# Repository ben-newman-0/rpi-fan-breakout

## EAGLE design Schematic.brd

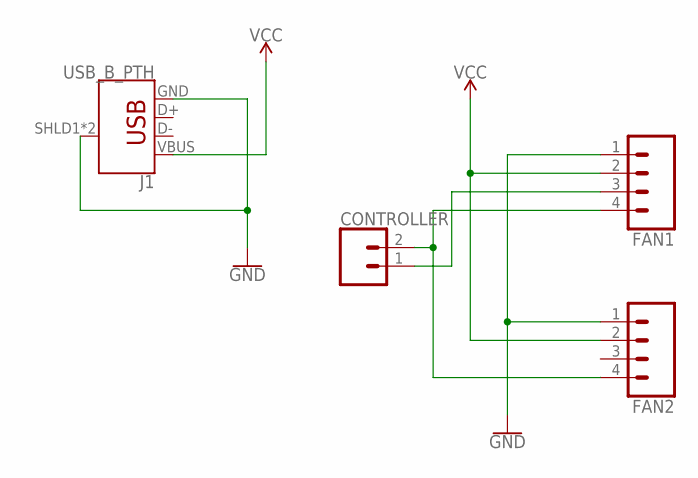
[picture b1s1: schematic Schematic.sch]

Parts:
CONTROLLER: CONN_02; 1X02
FAN1, FAN2: CONN_04POLAR; MOLEX-1X4
J1: USB_B_PTH; USB-B-PTH

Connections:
GND: FAN1.1, FAN2.1, J1.GND, J1.SHLD1 (SHIELD), J1.SHLD2 (SHIELD)
unnamed: CONTROLLER.1, FAN1.3
unnamed: CONTROLLER.2, FAN1.4, FAN2.4
VCC: FAN1.2, FAN2.2, J1.VBUS

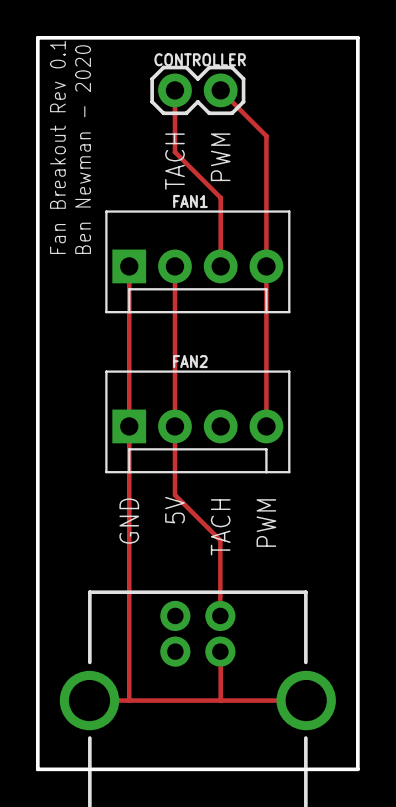
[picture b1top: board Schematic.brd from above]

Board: 2 copper layers, 17.8 x 40.6 mm, 4 parts (0 on the bottom side), 4 nets.

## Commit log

2020-12-30 Add initial PCB revision

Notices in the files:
parts and their libraries:
SparkFun-Connectors: Licensing: Creative Commons ShareAlike 4.0 International - https://creativecommons.org/licenses/by-sa/4.0
